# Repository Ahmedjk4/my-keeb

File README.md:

# my-keeb

A custom 60% mechanical keyboard that I designed from scratch, sponsored by Hack Club ❤️
### Each step is also found in commits with description

## Planning the Keyboard

I started by deciding on the layout and then decided what I wanted to include. I decided to include rgb leds, a rotary encoder, and a buzzer.
Took me about 15 minutes or less

## Designing the PCB

I designed the schematic and PCB in KiCad. This was one of the hardest parts because it was my first time designing a PCB.
This holy step took more than 12 hours

## Designing the Case

After finishing the PCB, I designed a 3D-printed case around it using Onshape.
Took me 6 hours because of the constrains tools always mess up when I try to move a sketch rectangle to fit the key.

Here is my [Onshape Model](https://cad.onshape.com/documents/ac0d0c8a76d47f62a8847ed2/w/3e72c33e2d57221932c06f57/e/e20cd8668801a9152e116827)

## Writing the Firmware

Finally, I wrote the keyboard firmware using RMK firmware ( didn't write it I actually edited a .toml file ) and built it on github actions, on my repo https://github.com/Ahmedjk4/custom-keyboard-firmware/

## What I Learnt

I learnt a lot about PCB design, CAD, and embedded keyboard firmware.

Thanks to Hack Club for sponsoring the project! ❤️

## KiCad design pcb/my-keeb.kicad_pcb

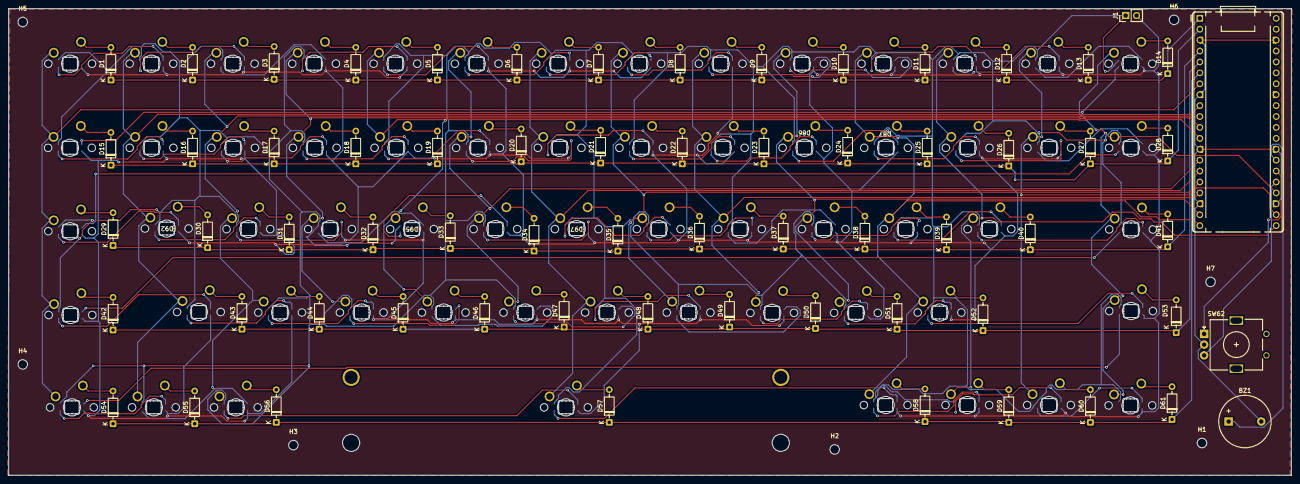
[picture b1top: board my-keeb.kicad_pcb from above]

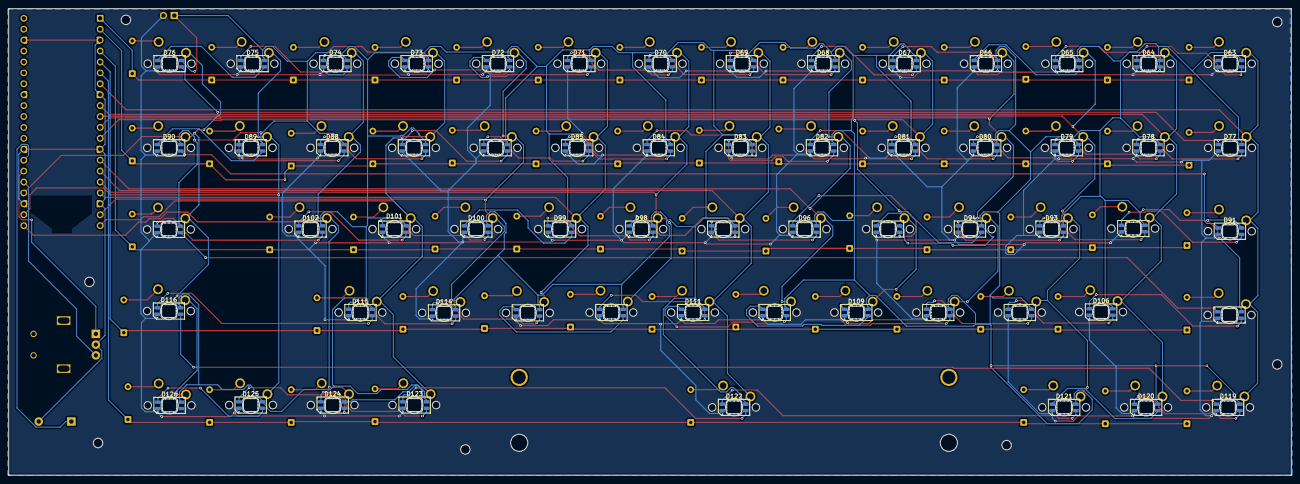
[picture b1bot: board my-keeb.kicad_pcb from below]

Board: 2 copper layers, 298.6 x 108.6 mm, 195 parts (61 on the bottom side), 146 nets.

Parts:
A1: RaspberryPi_Pico; RaspberryPi_Pico_Common_THT
BZ1: Buzzer; Buzzer_12x9.5RM7.6
D1, D2, D3, D4, D5, D6, D7, D8, D9, D10, D11, D12, D13, D14, D15, D16, D17, D18, D19, D20, D21, D22, D23, D24, D25, D26, D27, D28, D29, D30, D31, D32, D33, D34, D35, D36, D37, D38, D39, D40, D41, D42, D43, D44, D45, D46, D47, D48, D49, D50, D51, D52, D53, D54, D55, D56, D57, D58, D59, D60, D61: 1N4148; D_DO-35_SOD27_P7.62mm_Horizontal
D63, D64, D65, D66, D67, D68, D69, D70, D71, D72, D73, D74, D75, D76, D77, D78, D79, D80, D81, D82, D83, D84, D85, D86, D87, D88, D89, D90, D91, D92, D93, D94, D95, D96, D97, D98, D99, D100, D101, D102, D103, D105, D106, D107, D108, D109, D110, D111, D112, D113, D114, D115, D116, D119, D120, D121, D122, D123, D124, D125, D126: SK6812MINI-E; LED_SK6812MINI-E_3.2x2.8mm_P1.5mm_ReverseMount
H1, H2, H3, H4, H5, H6, H7: MountingHole; MountingHole_2.2mm_M2
J1: Conn_01x02_Socket; PinHeader_1x02_P2.54mm_Vertical
S1: MX_stab; STAB_MX_P_6.25u
SW1, SW2, SW3, SW4, SW5, SW6, SW7, SW8, SW9, SW10, SW11, SW12, SW13, SW14, SW15, SW16, SW17, SW18, SW19, SW20, SW21, SW22, SW23, SW24, SW25, SW26, SW27, SW28, SW29, SW30, SW31, SW32, SW33, SW34, SW35, SW36, SW37, SW38, SW39, SW40, SW41, SW42, SW43, SW44, SW45, SW46, SW47, SW48, SW49, SW50, SW51, SW52, SW53, SW54, SW55, SW56, SW57, SW58, SW59, SW60, SW61: SW_Push; SW_MX_1u
SW62: RotaryEncoder; RotaryEncoder_Alps_EC11E_Vertical_H20mm

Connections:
+5V: D63.3 (VDD), D64.3 (VDD), D65.3 (VDD), D66.3 (VDD), D67.3 (VDD), D68.3 (VDD), D69.3 (VDD), D70.3 (VDD), D71.3 (VDD), D72.3 (VDD), D73.3 (VDD), D74.3 (VDD), D75.3 (VDD), D76.3 (VDD), D77.3 (VDD), D78.3 (VDD), D79.3 (VDD), D80.3 (VDD), D81.3 (VDD), D82.3 (VDD), D83.3 (VDD), D84.3 (VDD), D85.3 (VDD), D86.3 (VDD), D87.3 (VDD), D88.3 (VDD), D89.3 (VDD), D90.3 (VDD), D91.3 (VDD), D92.3 (VDD), D93.3 (VDD), D94.3 (VDD), D95.3 (VDD), D96.3 (VDD), D97.3 (VDD), D98.3 (VDD), D99.3 (VDD), D100.3 (VDD), D101.3 (VDD), D102.3 (VDD), D103.3 (VDD), D105.3 (VDD), D106.3 (VDD), D107.3 (VDD), D108.3 (VDD), D109.3 (VDD), D110.3 (VDD), D111.3 (VDD), D112.3 (VDD), D113.3 (VDD), D114.3 (VDD), D115.3 (VDD), D116.3 (VDD), D119.3 (VDD), D120.3 (VDD), D121.3 (VDD), D122.3 (VDD), D123.3 (VDD), D124.3 (VDD), D125.3 (VDD), D126.3 (VDD), J1.1
/Root/COL0: A1.7 (GPIO5), SW1.1, SW15.1, SW29.1, SW42.1, SW54.1
/Root/COL1: A1.9 (GPIO6), SW2.1, SW16.1, SW30.1, SW43.1, SW55.1
/Root/COL2: A1.10 (GPIO7), SW3.1, SW17.1, SW31.1, SW44.1, SW56.1
/Root/COL3: A1.11 (GPIO8), SW4.1, SW18.1, SW32.1, SW45.1
/Root/COL4: A1.12 (GPIO9), SW5.1, SW19.1, SW33.1, SW46.1
/Root/COL5: A1.14 (GPIO10), SW6.1, SW20.1, SW34.1, SW47.1
/Root/COL6: A1.15 (GPIO11), SW7.1, SW21.1, SW35.1, SW48.1, SW57.1
/Root/COL7: A1.16 (GPIO12), SW8.1, SW22.1, SW36.1, SW49.1
/Root/COL8: A1.17 (GPIO13), SW9.1, SW23.1, SW37.1, SW50.1
/Root/COL9: A1.19 (GPIO14), SW10.1, SW24.1, SW38.1, SW51.1
/Root/COL10: A1.20 (GPIO15), SW11.1, SW25.1, SW39.1, SW52.1, SW58.1
/Root/COL11: A1.21 (GPIO16), SW12.1, SW26.1, SW40.1, SW59.1
/Root/COL12: A1.22 (GPIO17), SW13.1, SW27.1, SW60.1
/Root/COL13: A1.24 (GPIO18), SW14.1, SW28.1, SW41.1, SW53.1, SW61.1
/Root/ROW0: A1.1 (GPIO0), D1.1 (K), D2.1 (K), D3.1 (K), D4.1 (K), D5.1 (K), D6.1 (K), D7.1 (K), D8.1 (K), D9.1 (K), D10.1 (K), D11.1 (K), D12.1 (K), D13.1 (K), D14.1 (K)
/Root/ROW1: A1.2 (GPIO1), D15.1 (K), D16.1 (K), D17.1 (K), D18.1 (K), D19.1 (K), D20.1 (K), D21.1 (K), D22.1 (K), D23.1 (K), D24.1 (K), D25.1 (K), D26.1 (K), D27.1 (K), D28.1 (K)
/Root/ROW2: A1.4 (GPIO2), D29.1 (K), D30.1 (K), D31.1 (K), D32.1 (K), D33.1 (K), D34.1 (K), D35.1 (K), D36.1 (K), D37.1 (K), D38.1 (K), D39.1 (K), D40.1 (K), D41.1 (K)
/Root/ROW3: A1.5 (GPIO3), D42.1 (K), D43.1 (K), D44.1 (K), D45.1 (K), D46.1 (K), D47.1 (K), D48.1 (K), D49.1 (K), D50.1 (K), D51.1 (K), D52.1 (K), D53.1 (K)
/Root/ROW4: A1.6 (GPIO4), D54.1 (K), D55.1 (K), D56.1 (K), D57.1 (K), D58.1 (K), D59.1 (K), D60.1 (K), D61.1 (K)
GND: D63.1 (VSS), D64.1 (VSS), D65.1 (VSS), D66.1 (VSS), D67.1 (VSS), D68.1 (VSS), D69.1 (VSS), D70.1 (VSS), D71.1 (VSS), D72.1 (VSS), D73.1 (VSS), D74.1 (VSS), D75.1 (VSS), D76.1 (VSS), D77.1 (VSS), D78.1 (VSS), D79.1 (VSS), D80.1 (VSS), D81.1 (VSS), D82.1 (VSS), D83.1 (VSS), D84.1 (VSS), D85.1 (VSS), D86.1 (VSS), D87.1 (VSS), D88.1 (VSS), D89.1 (VSS), D90.1 (VSS), D91.1 (VSS), D92.1 (VSS), D93.1 (VSS), D94.1 (VSS), D95.1 (VSS), D96.1 (VSS), D97.1 (VSS), D98.1 (VSS), D99.1 (VSS), D100.1 (VSS), D101.1 (VSS), D102.1 (VSS), D103.1 (VSS), D105.1 (VSS), D106.1 (VSS), D107.1 (VSS), D108.1 (VSS), D109.1 (VSS), D110.1 (VSS), D111.1 (VSS), D112.1 (VSS), D113.1 (VSS), D114.1 (VSS), D115.1 (VSS), D116.1 (VSS), D119.1 (VSS), D120.1 (VSS), D121.1 (VSS), D122.1 (VSS), D123.1 (VSS), D124.1 (VSS), D125.1 (VSS), D126.1 (VSS), J1.2
unnamed: A1.25 (GPIO19), SW62.B
unnamed: A1.26 (GPIO20), SW62.A
unnamed: A1.27 (GPIO21), BZ1.1 (+)
unnamed: A1.3 (GND), A1.8 (GND), A1.13 (GND), A1.18 (GND), A1.23 (GND), A1.28 (GND), A1.38 (GND), BZ1.2 (-), SW62.C
unnamed: D1.2 (A), SW1.2
unnamed: D2.2 (A), SW2.2
unnamed: D3.2 (A), SW3.2
unnamed: D4.2 (A), SW4.2
unnamed: D5.2 (A), SW5.2
unnamed: D6.2 (A), SW6.2
unnamed: D7.2 (A), SW7.2
unnamed: D8.2 (A), SW8.2
unnamed: D9.2 (A), SW9.2
unnamed: D10.2 (A), SW10.2
unnamed: D11.2 (A), SW11.2
unnamed: D12.2 (A), SW12.2
unnamed: D13.2 (A), SW13.2
unnamed: D14.2 (A), SW14.2
unnamed: D15.2 (A), SW15.2
unnamed: D16.2 (A), SW16.2
unnamed: D17.2 (A), SW17.2
unnamed: D18.2 (A), SW18.2
unnamed: D19.2 (A), SW19.2
unnamed: D20.2 (A), SW20.2
unnamed: D21.2 (A), SW21.2
unnamed: D22.2 (A), SW22.2
unnamed: D23.2 (A), SW23.2
unnamed: D24.2 (A), SW24.2
unnamed: D25.2 (A), SW25.2
unnamed: D26.2 (A), SW26.2
unnamed: D27.2 (A), SW27.2
unnamed: D28.2 (A), SW28.2
unnamed: D29.2 (A), SW29.2
unnamed: D30.2 (A), SW30.2
unnamed: D31.2 (A), SW31.2
unnamed: D32.2 (A), SW32.2
unnamed: D33.2 (A), SW33.2
unnamed: D34.2 (A), SW34.2
unnamed: D35.2 (A), SW35.2
unnamed: D36.2 (A), SW36.2
unnamed: D37.2 (A), SW37.2
unnamed: D38.2 (A), SW38.2
unnamed: D39.2 (A), SW39.2
unnamed: D40.2 (A), SW40.2
unnamed: D41.2 (A), SW41.2
unnamed: D42.2 (A), SW42.2
unnamed: D43.2 (A), SW43.2
unnamed: D44.2 (A), SW44.2
unnamed: D45.2 (A), SW45.2
unnamed: D46.2 (A), SW46.2
unnamed: D47.2 (A), SW47.2
unnamed: D48.2 (A), SW48.2
unnamed: D49.2 (A), SW49.2
unnamed: D50.2 (A), SW50.2
unnamed: D51.2 (A), SW51.2
unnamed: D52.2 (A), SW52.2
unnamed: D53.2 (A), SW53.2
unnamed: D54.2 (A), SW54.2
unnamed: D55.2 (A), SW55.2
unnamed: D56.2 (A), SW56.2
unnamed: D57.2 (A), SW57.2
unnamed: D58.2 (A), SW58.2
unnamed: D59.2 (A), SW59.2
unnamed: D60.2 (A), SW60.2
unnamed: D61.2 (A), SW61.2
unnamed: D63.4 (DOUT), D64.2 (DIN)
unnamed: D64.4 (DOUT), D65.2 (DIN)
unnamed: D65.4 (DOUT), D66.2 (DIN)
unnamed: D66.4 (DOUT), D67.2 (DIN)
unnamed: D67.4 (DOUT), D68.2 (DIN)
unnamed: D68.4 (DOUT), D69.2 (DIN)
unnamed: D69.4 (DOUT), D70.2 (DIN)
unnamed: D70.4 (DOUT), D71.2 (DIN)
unnamed: D71.4 (DOUT), D72.2 (DIN)
unnamed: D72.4 (DOUT), D73.2 (DIN)
unnamed: D73.4 (DOUT), D74.2 (DIN)
unnamed: D74.4 (DOUT), D75.2 (DIN)
unnamed: D75.4 (DOUT), D76.2 (DIN)
unnamed: D76.4 (DOUT), D77.2 (DIN)
unnamed: D77.4 (DOUT), D78.2 (DIN)
unnamed: D78.4 (DOUT), D79.2 (DIN)
unnamed: D79.4 (DOUT), D80.2 (DIN)
unnamed: D80.4 (DOUT), D81.2 (DIN)
unnamed: D81.4 (DOUT), D82.2 (DIN)
unnamed: D82.4 (DOUT), D83.2 (DIN)
unnamed: D83.4 (DOUT), D84.2 (DIN)
unnamed: D84.4 (DOUT), D85.2 (DIN)
unnamed: D85.4 (DOUT), D86.2 (DIN)
unnamed: D86.4 (DOUT), D87.2 (DIN)
unnamed: D87.4 (DOUT), D88.2 (DIN)
unnamed: D88.4 (DOUT), D89.2 (DIN)
unnamed: D89.4 (DOUT), D90.2 (DIN)
unnamed: D90.4 (DOUT), D91.2 (DIN)
unnamed: D91.4 (DOUT), D92.2 (DIN)
unnamed: D92.4 (DOUT), D93.2 (DIN)
unnamed: D93.4 (DOUT), D94.2 (DIN)
unnamed: D94.4 (DOUT), D95.2 (DIN)
unnamed: D95.4 (DOUT), D96.2 (DIN)
unnamed: D96.4 (DOUT), D97.2 (DIN)
unnamed: D97.4 (DOUT), D98.2 (DIN)
unnamed: D98.4 (DOUT), D99.2 (DIN)
unnamed: D99.4 (DOUT), D100.2 (DIN)
unnamed: D100.4 (DOUT), D101.2 (DIN)
unnamed: D101.4 (DOUT), D102.2 (DIN)
unnamed: D102.4 (DOUT), D103.2 (DIN)
unnamed: D103.4 (DOUT), D105.2 (DIN)
unnamed: D105.4 (DOUT), D106.2 (DIN)
unnamed: D106.4 (DOUT), D107.2 (DIN)
unnamed: D107.4 (DOUT), D108.2 (DIN)
unnamed: D108.4 (DOUT), D109.2 (DIN)
unnamed: D109.4 (DOUT), D110.2 (DIN)
unnamed: D110.4 (DOUT), D111.2 (DIN)
unnamed: D111.4 (DOUT), D112.2 (DIN)
unnamed: D112.4 (DOUT), D113.2 (DIN)
unnamed: D113.4 (DOUT), D114.2 (DIN)
unnamed: D114.4 (DOUT), D115.2 (DIN)
unnamed: D115.4 (DOUT), D116.2 (DIN)
unnamed: D116.4 (DOUT), D119.2 (DIN)
unnamed: D119.4 (DOUT), D120.2 (DIN)
unnamed: D120.4 (DOUT), D121.2 (DIN)
unnamed: D121.4 (DOUT), D122.2 (DIN)
unnamed: D122.4 (DOUT), D123.2 (DIN)
unnamed: D123.4 (DOUT), D124.2 (DIN)
unnamed: D124.4 (DOUT), D125.2 (DIN)
unnamed: D125.4 (DOUT), D126.2 (DIN)
